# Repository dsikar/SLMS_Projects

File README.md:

# SLMS_Projects

## Projects I have been working on at the [South London Makerspace] (http://southlondonmakerspace.org/) 

# MQ-4 methane gas sensor.

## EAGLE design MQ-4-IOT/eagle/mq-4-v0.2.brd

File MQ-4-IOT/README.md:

MQ-4 IOT
==============

Methane CNG Gas Sensor Internet of Things device.  

[MQ-4 Datasheet] (https://www.sparkfun.com/datasheets/Sensors/Biometric/MQ-4.pdf)  
[DHT22 Datasheet (temp/hum sensor)] (http://www.electroschematics.com/wp-content/uploads/2015/02/DHT22-datasheet.pdf)  
[AM2302 Datasheet (temp/hum sensor)] (https://cdn-shop.adafruit.com/datasheets/Digital+humidity+and+temperature+sensor+AM2302.pdf)

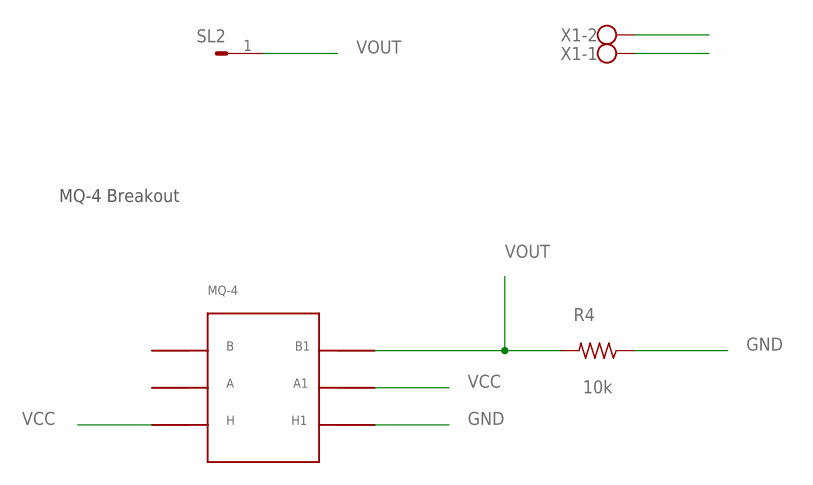
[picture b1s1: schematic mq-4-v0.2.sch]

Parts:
R4: 10k; 0207/10
SL2: M0201P; 02P
U$1: MQ-4
X1: W237-102

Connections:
GND: R4.1, U$1.H1, X1.2
VCC: U$1.A1, U$1.H, X1.1
VOUT: R4.2, SL2.1, U$1.B1

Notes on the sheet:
MQ-4 Breakout

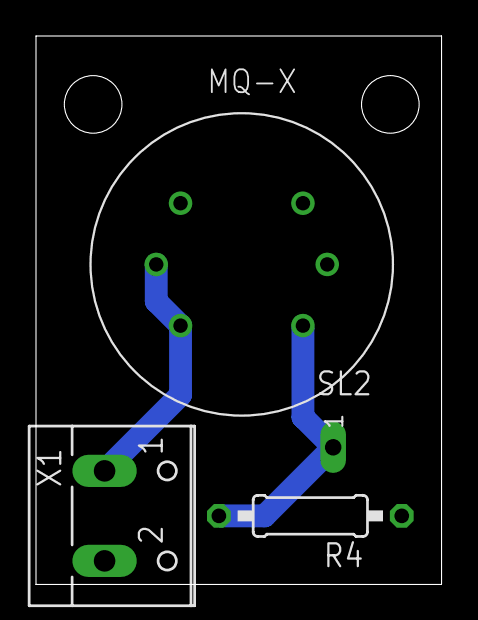
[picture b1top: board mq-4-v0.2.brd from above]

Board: 2 copper layers, 22.5 x 30.5 mm, 4 parts (0 on the bottom side), 3 nets.

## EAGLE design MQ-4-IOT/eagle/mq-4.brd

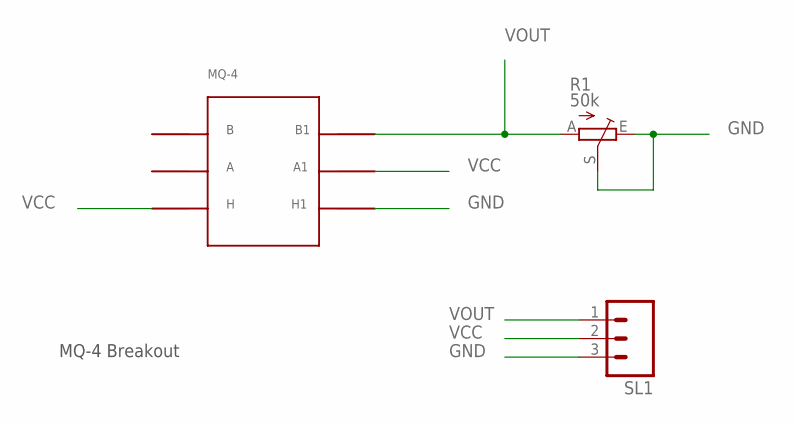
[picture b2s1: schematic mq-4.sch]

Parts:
R1: 50k; B64Y
SL1: M03; 03P
U$1: MQ-4

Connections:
GND: R1.E, R1.S, SL1.3, U$1.H1
VCC: SL1.2, U$1.A1, U$1.H
VOUT: R1.A, SL1.1, U$1.B1

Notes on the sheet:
MQ-4 Breakout

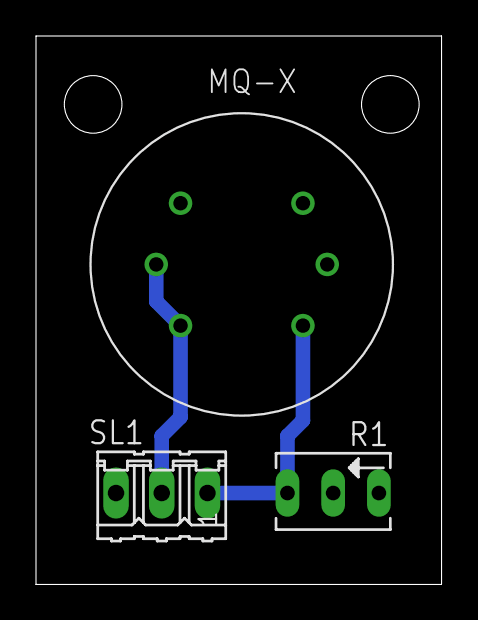
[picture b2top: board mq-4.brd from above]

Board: 2 copper layers, 22.5 x 30.5 mm, 3 parts (0 on the bottom side), 3 nets.

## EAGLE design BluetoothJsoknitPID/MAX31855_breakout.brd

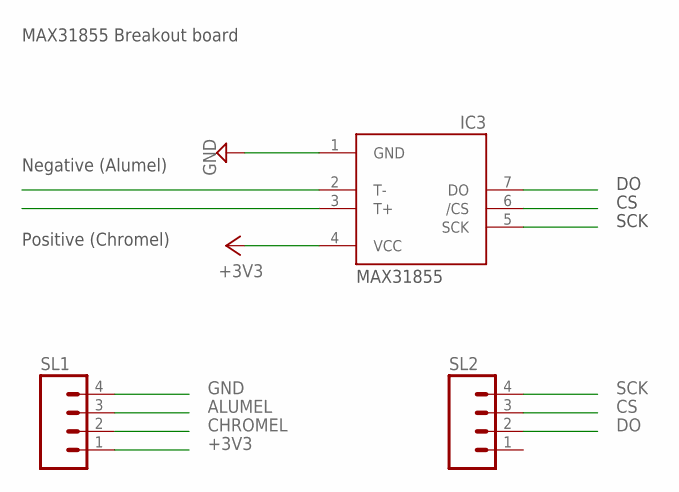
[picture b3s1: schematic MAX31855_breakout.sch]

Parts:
IC3: MAX6675; SO08
SL1, SL2: M04; 04P

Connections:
+3V3: IC3.4 (VCC), SL1.1
ALUMEL: IC3.2 (T-), SL1.3
CHROMEL: IC3.3 (T+), SL1.2
CS: IC3.6 (/CS), SL2.3
DO: IC3.7 (DO), SL2.2
GND: IC3.1 (GND), SL1.4
SCK: IC3.5 (SCK), SL2.4

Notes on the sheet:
SCK
Positive (Chromel)
Negative (Alumel)
MAX31855
MAX31855 Breakout board

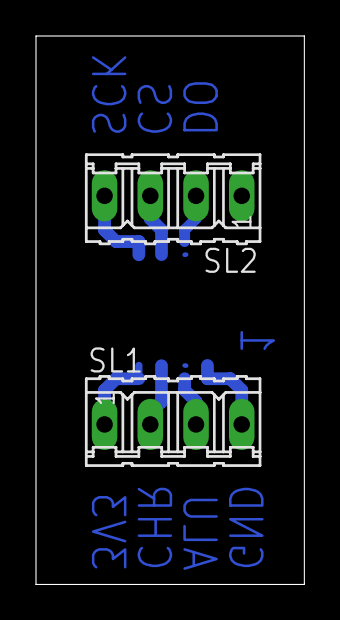
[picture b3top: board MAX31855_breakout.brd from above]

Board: 2 copper layers, 14.9 x 30.5 mm, 3 parts (1 on the bottom side), 7 nets.

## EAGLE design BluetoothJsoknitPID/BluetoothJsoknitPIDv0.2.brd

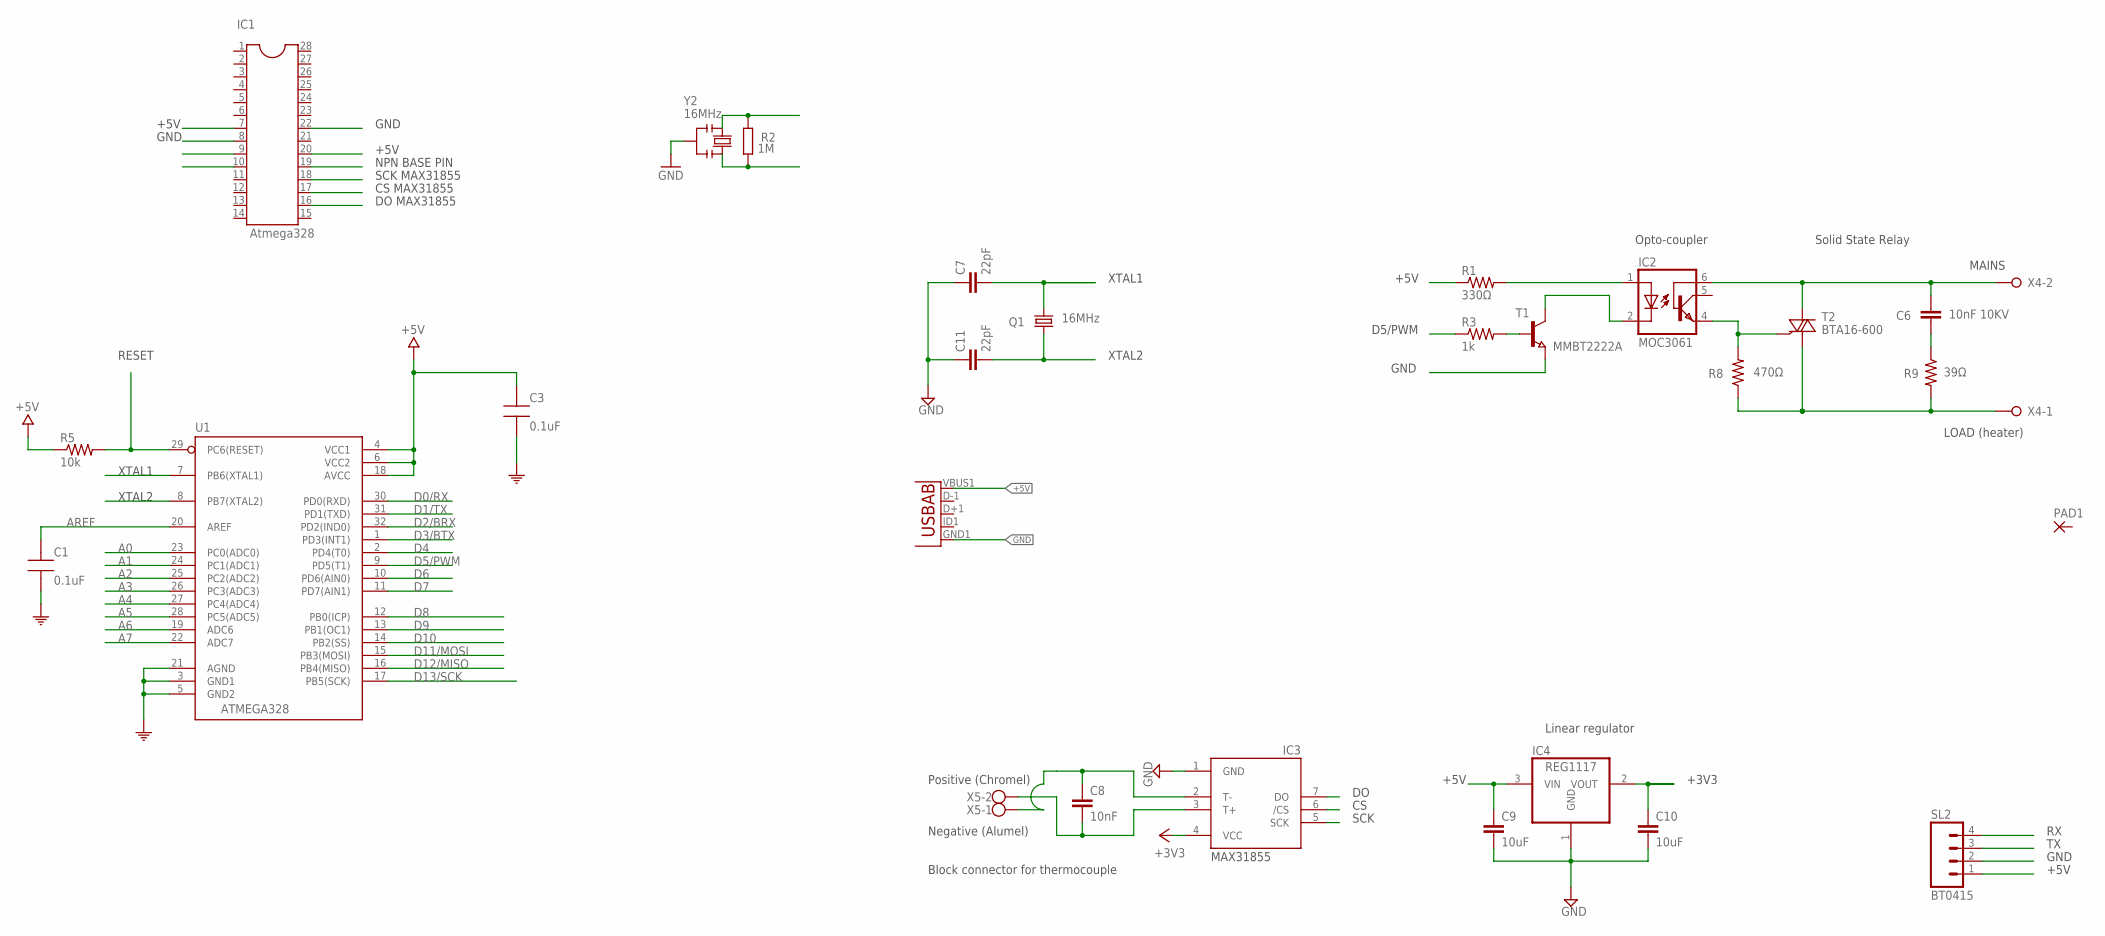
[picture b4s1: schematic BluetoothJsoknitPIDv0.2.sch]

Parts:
C1, C3: 0.1uF; CAP0805-NP
C6: 10nF 10KV; C050-025X075
C7, C11: 22pF; C0805
C8: 10nF; C0805
C9, C10: 10uF; 1206
IC1: Atmega328; DIL28-3
IC2: MOC3061; DIL6-SMD
IC3: MAX6675; SO08
IC4: REG1117; SOT223
PAD1: SMD2; SMD1,27-2,54
Q1: 16MHz; HC49/S
R1: 330Ω; M0805
R2: 1M; R0603-ROUND
R3: 1k; M0805
R5: 10k; M0805
R8: 470Ω; 0207/10
R9: 39Ω; 0207/10
SL2: BT0415; 04P
T1: MMBT2222A; SOT23
T2: BTA16-600; TO220BV
U1: ATMEGA328; QFP032
U$4: USB-AB""; USB-AB-MICRO-SMD_V02_BOSS
X4: W237-02P; W237-132
X5: W237-102
Y2: 16MHz; RESONATOR

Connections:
+3V3: C10.1, IC3.4 (VCC), IC4.2 (VOUT)
+5V: C3.1, C9.1, IC1.7, IC1.20, IC4.3 (VIN), R1.1, R5.1, SL2.1, U1.4 (VCC1), U1.6 (VCC2), U1.18 (AVCC), U$4.VBUS1 (VBUS)
A0: U1.23 (PC0(ADC0))
A1: U1.24 (PC1(ADC1))
A2: U1.25 (PC2(ADC2))
A3: U1.26 (PC3(ADC3))
A4: U1.27 (PC4(ADC4))
A5: U1.28 (PC5(ADC5))
A6: U1.19 (ADC6)
A7: U1.22 (ADC7)
AREF: C1.1, U1.20 (AREF)
COM: C1.2, C3.2, U1.3 (GND1), U1.5 (GND2), U1.21 (AGND)
CS: IC1.17, IC3.6 (/CS)
D0/RX: U1.30 (PD0(RXD))
D1/TX: U1.31 (PD1(TXD))
D2/BRX: U1.32 (PD2(IND0))
D3/BTX: U1.1 (PD3(INT1))
D4: U1.2 (PD4(T0))
D5/PWM: R3.1, U1.9 (PD5(T1))
D6: U1.10 (PD6(AIN0))
D7: U1.11 (PD7(AIN1))
D8: U1.12 (PB0(ICP))
D9: U1.13 (PB1(OC1))
D10: U1.14 (PB2(SS))
D11/MOSI: U1.15 (PB3(MOSI))
D12/MISO: U1.16 (PB4(MISO))
D13/SCK: U1.17 (PB5(SCK))
DO: IC1.16, IC3.7 (DO)
GND: C7.1, C9.2, C10.2, C11.1, IC1.8, IC1.22, IC3.1 (GND), IC4.1 (GND), SL2.2, T1.2 (E), U$4.GND1 (GND), Y2.2
LOAD: R8.1, R9.2, T2.T1 (A1), X4.1
MOC3061PIN4: IC2.4 (EMI), R8.2, T2.G
MOC3061PIN6: C6.1, IC2.6 (BAS), T2.T2 (A2), X4.2
unnamed: IC2.2 (C), T1.3 (C)
unnamed: R3.2, T1.1 (B)
unnamed: IC2.1 (A), R1.2
unnamed: C6.2, R9.1
PWM: IC1.19
RESET: R5.2, U1.29 (PC6(RESET))
RX: SL2.4
SCK: IC1.18, IC3.5 (SCK)
T+1: C8.2, IC3.3 (T+), X5.2
T-1: C8.1, IC3.2 (T-), X5.1
TX: SL2.3
XTAL1: C7.2, IC1.9, Q1.2, U1.7 (PB6(XTAL1))
XTAL2: C11.2, IC1.10, Q1.1, U1.8 (PB7(XTAL2))
XTAL3: R2.2, Y2.1
XTAL4: R2.1, Y2.3

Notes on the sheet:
DO MAX31855
CS MAX31855
SCK MAX31855
NPN BASE PIN
+5V
GND
XTAL1
XTAL2
D5/PWM
LOAD (heater)
MAINS
Block connector for thermocouple
SCK
Positive (Chromel)
Negative (Alumel)
+3V3
Opto-coupler
Solid State Relay
Linear regulator
MAX31855
RESET

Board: 2 copper layers, 28 parts (0 on the bottom side), 23 nets, no tracks yet.

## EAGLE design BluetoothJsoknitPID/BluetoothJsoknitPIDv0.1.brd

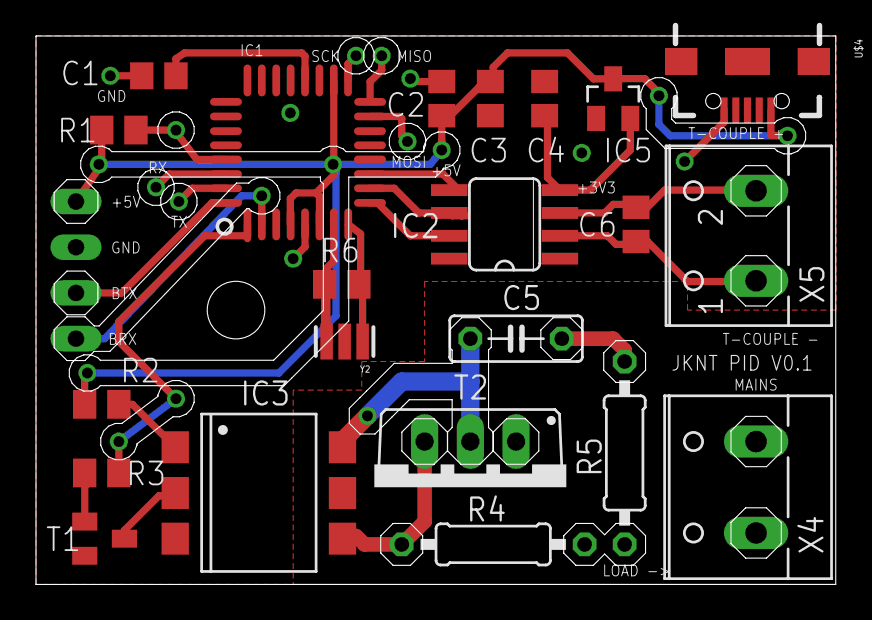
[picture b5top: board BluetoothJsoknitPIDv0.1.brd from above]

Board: 2 copper layers, 44.4 x 30.5 mm, 23 parts (1 on the bottom side), 22 nets.

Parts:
C1, C2: 0.1uF; C0805
C3, C4: 10uF; C0805
C5: 10nF 10KV; C050-025X075
C6: 10nF; C0805
IC1: ATMEGA328; QFP032
IC2: SO08
IC3: MOC3061; DIL6-SMD
IC5: MCP1703CB; SOT23
R1: 10k; M0805
R2: 330Ω; M0805
R3: 1k; M0805
R4: 470Ω; 0207/10
R5: 39Ω; 0207/10
R6: 1M; M0805
SL2: BT0415; 04P
T1: MMBT2222A; SOT23
T2: BTA16-600; TO220BV
U$4: USB-AB-MICRO-SMD_V02_BOSS
X4: W237-132
X5: W237-102
Y2: 16MHz; RESONATOR

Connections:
+3V3: C4.1, IC2.4, IC5.2
+5V: C2.1, C3.1, IC1.4, IC1.6, IC1.18, IC5.3, R1.1, R2.1, SL2.4, U$4.VBUS1
AREF: C1.1, IC1.20
D2/BTX: IC1.32, SL2.2
D3/PWM: IC1.1, R3.1
D4/BRX: IC1.2, SL2.1
D5/MAX31855DO: IC1.9, IC2.7
D6/MAX31855CS: IC1.10, IC2.6
D7/MAX31855SCK: IC1.11, IC2.5
GND: C1.2, C2.2, C3.2, C4.2, IC1.3, IC1.5, IC1.21, IC2.1, IC5.1, SL2.3, T1.2, U$4.GND1, Y2.2
LOAD: R4.1, R5.2, T2.T1, X4.1
MAINS: C5.1, IC3.6, T2.T2, X4.2
MOC3061PIN4: IC3.4, R4.2, T2.G
unnamed: IC3.2, T1.3
unnamed: R3.2, T1.1
unnamed: IC3.1, R2.2
unnamed: C5.2, R5.1
RESET: IC1.29, R1.2
T+: C6.2, IC2.3, X5.2
T-: C6.1, IC2.2
XTAL1: IC1.7, R6.1, Y2.3
XTAL2: IC1.8, R6.2, Y2.1

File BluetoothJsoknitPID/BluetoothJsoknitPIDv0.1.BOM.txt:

Partlist exported from C:/Users/danielsikar/Documents/eagle/SLMS_Projects/BluetoothJsoknitPID/BluetoothJsoknitPIDv0.1.sch at 23/09/2016 21:34

Part Value     Device               Package                   Description                                                                                                   MF                      MPN     OC_FARNELL OC_NEWARK
C1   0.1uF     C-EUC0805            C0805                     CAPACITOR, European symbol                                                                                                                                        
C2   0.1uF     C-EUC0805            C0805                     CAPACITOR, European symbol                                                                                                                                        
C3   10uF      C-EUC0805            C0805                     CAPACITOR, European symbol                                                                                                                                        
C4   10uF      C-EUC0805            C0805                     CAPACITOR, European symbol                                                                                                                                        
C5   10nF 10KV C-EU050-025X075      C050-025X075              CAPACITOR, European symbol                                                                                                                                        
C6   10nF      C-EUC0805            C0805                     CAPACITOR, European symbol                                                                                                                                        
IC1  ATMEGA328 ATMEGA168-20AU       QFP032                                                                                                                                                                                      
IC2            MAX6675              SO08                                                                                                                                                                                        
IC3  MOC3061   4N25SM               DIL6-SMD                  General Purpose 6-Pin Phototransistor Optocouplers                                                            FAIRCHILD SEMICONDUCTOR 4N25SM  1021152    34C2020  
IC5  MCP1703CB MCP1703CB            SOT23                     250 mA, 16V, Low Quiescent Current LDO Regulator                                                                                                                  
R1   10k       R-US_M0805           M0805                     RESISTOR, American symbol                                                                                                                                         
R2   330O      R-US_M0805           M0805                     RESISTOR, American symbol                                                                                                                                         
R3   1k        R-US_M0805           M0805                     RESISTOR, American symbol                                                                                                                                         
R4   470O      R-US_0207/10         0207/10                   RESISTOR, American symbol                                                                                                                                         
R5   39O       R-US_0207/10         0207/10                   RESISTOR, American symbol                                                                                                                                         
R6   1M        R-US_M0805           M0805                     RESISTOR, American symbol                                                                                                                                         
SL2   BT0415   M04                  04P                       AMP QUICK CONNECTOR                                                                                                                           unknown    unknown  
T1   MMBT2222A NPN-TRANSISTOR_SOT23 SOT23                     NPN TRANSISTOR                                                                                                                                                    
T2   BTA16-600 BT138-V              TO220BV                   TRIAC                                                                                                                                                             
U$4            USB-AB""             USB-AB-MICRO-SMD_V02_BOSS This is a USB AB connector that is compatible with USB OTG. i.e. this connector can serve as a host or device                                                     
X4             W237-02P             W237-132                  WAGO SREW CLAMP                                                                                                                               unknown    unknown  
X5             W237-102             W237-102                  WAGO SCREW CLAMP                                                                                                                      237-102 unknown    70K9898  NB Double check pitch for both screw clamps
Y2   16MHz     RESONATORMU          RESONATOR

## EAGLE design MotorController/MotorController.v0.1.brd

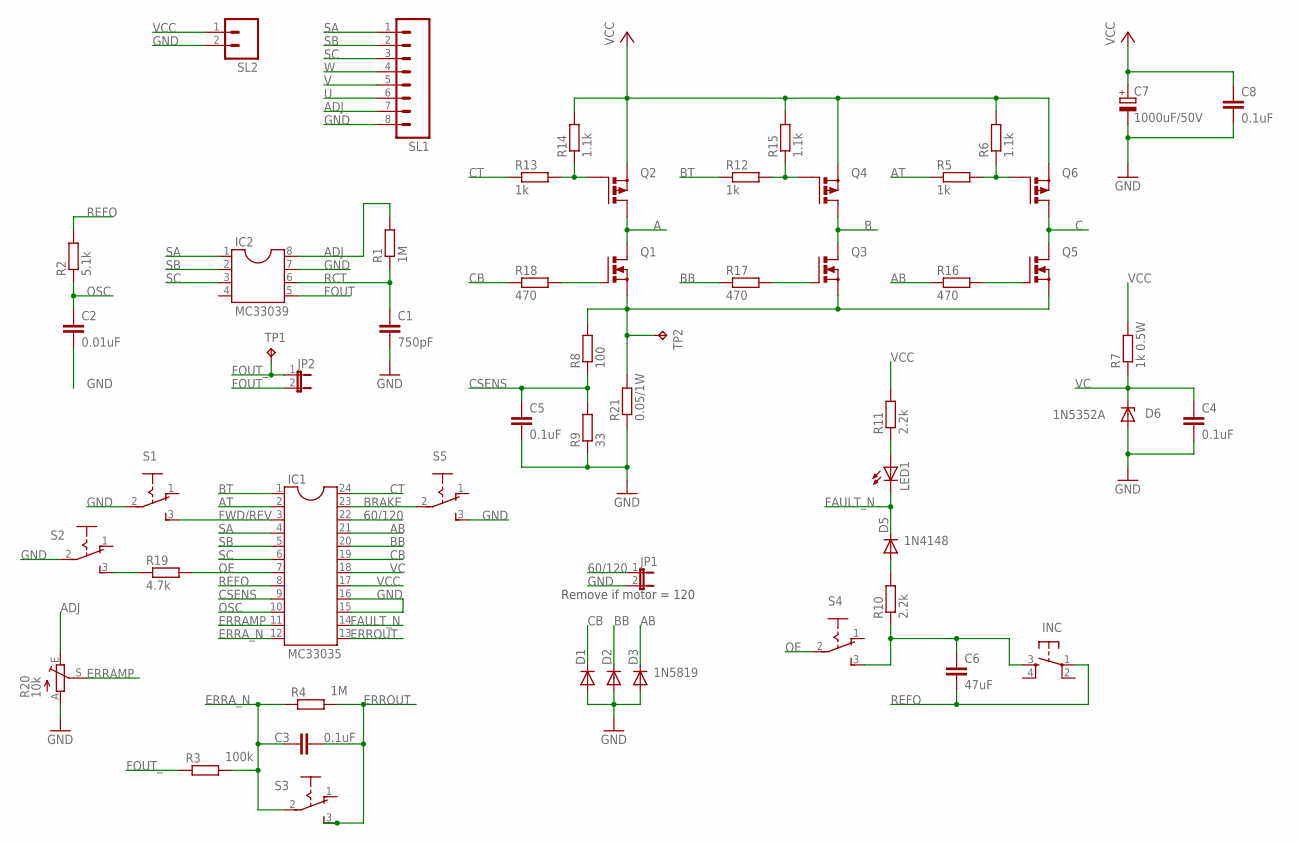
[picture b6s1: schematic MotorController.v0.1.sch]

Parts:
C1: 750pF; C025-025X050
C2: 0.01uF; C025-025X050
C3, C4, C5, C8: 0.1uF; C025-025X050
C6: 47uF; C025-025X050
C7: 1000uF/50V; E7,5-16
D1, D2: 1N4148DO35-7; DO35-7
D3: 1N5819; DO35-7
D5: 1N4148; DO35-7
D6: 1N5352A; DO34Z7
IC1: MC33035; DIL24-3
IC2: MC33039; SOCKET-08
INC: TAC_SWITCHPTH; TACTILE-PTH
JP1, JP2: JP1E; JP1
LED1: LEDLD260; LD260
Q1, Q3, Q5: PMOSFET_NTO220BV; TO220BV
Q2, Q4, Q6: PMOSFET_PTO220BV; TO220BV
R1, R4: 1M; 0204V
R2: 5.1k; 0204V
R3: 100k; 0204V
R5, R12, R13: 1k; 0204V
R6, R14, R15: 1.1k; 0204V
R7: 1k 0.5W; 0204V
R8: 100; 0204V
R9: 33; 0204V
R10, R11: 2.2k; 0204V
R16, R17, R18: 470; 0204V
R19: 4.7k; 0204V
R20: 10k; CA6V
R21: 0.05/1W; 0204V
S1, S2, S3, S4, S5: M251
SL1: M08; 08P
SL2: M02; 02P
TP1, TP2: TPPAD1-13Y; P1-13Y

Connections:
60/120: IC1.22, JP1.1
A: Q1.D, Q2.D
AB: D3.C, IC1.21, R16.1
ADJ: IC2.8, R1.2, R20.E, SL1.7
AT: IC1.2, R5.1
B: Q3.D, Q4.D
BB: D2.C, IC1.20, R17.1
BRAKE: IC1.23, S5.2
BT: IC1.1, R12.1
C: Q5.D, Q6.D
CB: D1.C, IC1.19, R18.1
CSENS: C5.1, IC1.9, R8.1, R9.2
CT: IC1.24, R13.1
ERRAMP: IC1.11, R20.S
ERRA_N: C3.1, IC1.12, R3.2, R4.1, S3.2
ERROUT: C3.2, IC1.13, R4.2, S3.3 (S)
FAULT_N: D5.C, IC1.14, LED1.K (C)
FOUT: IC2.5, JP2.2
FOUT_: JP2.1, R3.1, TP1.TP
FWD/REV: IC1.3, S1.3 (S)
GND: C1.2, C2.2, C4.2, C5.2, C7.-, C8.2, D1.A, D2.A, D3.A, D6.A, IC1.15, IC1.16, IC2.7, JP1.2, R9.1, R20.A, R21.1, S1.2, S2.2, S5.3 (S), SL1.8, SL2.2
unnamed: R19.1, S2.3 (S)
unnamed: LED1.A, R11.1
unnamed: Q3.G, R17.2
unnamed: Q5.G, R16.2
unnamed: Q6.G, R5.2, R6.1
unnamed: D5.A, R10.2
unnamed: Q1.S, Q3.S, Q5.S, R8.2, R21.2, TP2.TP
unnamed: Q4.G, R12.2, R15.1
unnamed: Q2.G, R13.2, R14.1
unnamed: Q1.G, R18.2
unnamed: C6.1, INC.3, R10.1, S4.3 (S)
OE: IC1.7, R19.2, S4.2
OSC: C2.1, IC1.10, R2.1
RCT: C1.1, IC2.6, R1.1
REFO: C6.2, IC1.8, INC.1, R2.2
SA: IC1.4, IC2.1, SL1.1
SB: IC1.5, IC2.2, SL1.2
SC: IC1.6, IC2.3, SL1.3
U: SL1.6
V: SL1.5
VC: C4.1, D6.C, IC1.18, R7.1
VCC: C7.+, C8.1, IC1.17, Q2.S, Q4.S, Q6.S, R6.2, R7.2, R11.2, R14.2, R15.2, SL2.1
W: SL1.4

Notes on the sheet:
Remove if motor = 120

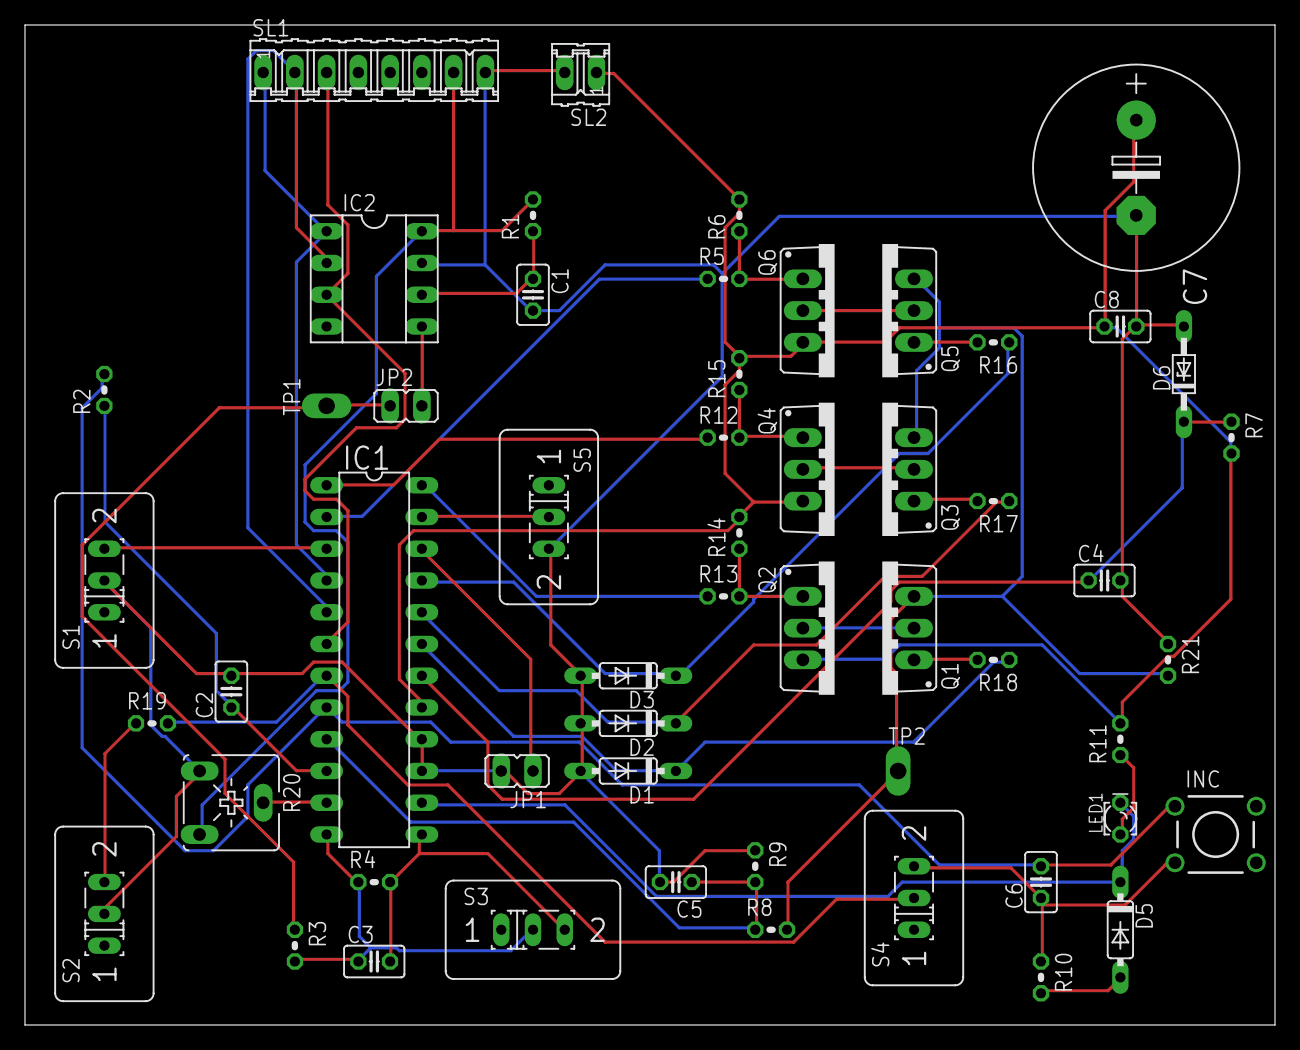
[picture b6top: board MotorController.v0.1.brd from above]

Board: 2 copper layers, 100.0 x 80.0 mm, 55 parts (0 on the bottom side), 41 nets.

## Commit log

2016-06-28 Initial commit.
2016-07-02 Adding.
2016-07-02 Image + version.
2016-07-03 Folder rename.
2016-07-03 Added board.
2016-09-12 General reshuffle plus added schematic sketch.
2016-09-17 Added circuits for Ted in China.
2016-09-22 Added stencil .dxf
2016-09-22 Added solder paste stencil mask .pdf
2016-09-23 Added v0.1 BOM.
2016-09-29 BOM screw clamp pitch note
2016-10-11 PCB fabrication files.
2016-10-11 Tweaked .pdf and .dxf for Trotec laser printer.
2016-10-11 Solid infill .pdf for laser cutter.
2016-10-13 Added more laserable solder masks.
2016-10-13 Removed dxf.
2016-10-13 Solid fill.
2016-10-13 Solid fill with 3 mill spacing on pads (6 mil narrower).
2016-10-13 Added 1 mil padding pdf solder mask.
2016-10-17 Minimal description.
2016-10-17 Ignoring Mouser BOMs for now.
2016-10-17 Started MQ-4-IOT gig.
2016-10-17 Added datasheet.
2016-10-17 Added Power module BOM.
2016-10-17 changed .txt to .md for added interactivity.
2016-10-17 Added LiPO charger image.
2016-10-17 Solar panel, buck regulator images.
2016-10-17 Added separate sensor BOM.
2016-10-17 More datasheets.
2016-10-17 Cosmetics
2016-10-17 Added custom eagle library for MQ-4.
2016-10-18 MQ-4 breakout added.
2016-10-18 Added CAM files.
2016-10-18 Added camotics toolpath simulation.
2016-10-18 Added Shapeoko/GRBL notes.
2016-10-18 Added first milling attempt.
2016-10-19 Added enclosure files.
2016-10-19 Outline milling file.
2016-10-19 General housekeeping.
2016-10-19 Increased area.
2016-10-19 Via web interface as backup.
2016-10-20 Outlines for milling.
2016-10-20 General tidy up.
2016-10-20 Another enclosure iteration.
2016-10-20 Added first draft sketch.
2016-10-21 More files to .gitignore.
2016-10-21 Enclosure with circular wire hole on top side.
2016-10-21 Move wire gap to top part.
2016-10-23 NodeMCU + MQ-4 enclosure.
2016-10-25 Added v0.2 with added power up options.
2016-10-25 Added enclosure top half.
2016-10-25 More tool paths.
2016-10-25 Board update.
2016-10-26 Removed block connector gap.
2016-10-26 Documentation.
2016-10-26 Diameter tests for Ultimaker 2.
2016-10-26 MQ-7 enclosure and ThingSpeak code.
2016-10-26 MQ-4 enclosure g-code.
2016-10-28 Rounded shelled enclosure printing tests.
2016-10-28 MQ-4 hollowed enclosures.
2016-10-28 Added MQ-4 shelled enclosure.
2016-10-29 Two part shelled enclosure.

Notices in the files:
parts and their libraries:
SparkFun-Capacitors: Licensing: Creative Commons ShareAlike 4.0 International - https://creativecommons.org/licenses/by-sa/4.0
